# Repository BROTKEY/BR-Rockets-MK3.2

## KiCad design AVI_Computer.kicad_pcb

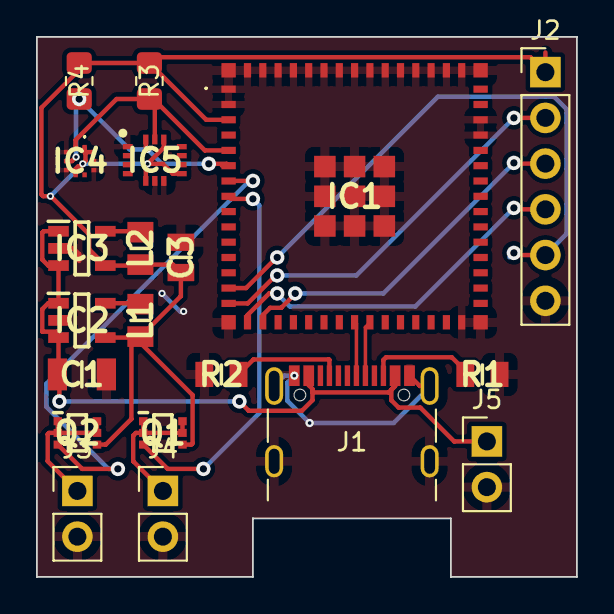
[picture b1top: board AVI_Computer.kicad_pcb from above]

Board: 2 copper layers, 30.0 x 30.0 mm, 20 parts (0 on the bottom side), 19 nets.

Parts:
C1: EMK316B7475KL-T; CAPC3216X180N
C3: TMK212BBJ106KG-T; CAPC2114X145N
IC1: ESP32-S2-MINI-2U-N4; ESP32S2MINI2UN4
IC2, IC3: LM3671MF-3.3_NOPB; SOT95P284X119-5N
IC4: BMP390
IC5: BMI270; QFN50P300X250X87-14N
J1: USB4105-GF-A-060; USB_C_Receptacle_GCT_USB4105-xx-A_16P_TopMnt_Horizontal
J2: Conn_01x06_Pin; PinHeader_1x06_P2.54mm_Vertical
J3, J4, J5: Conn_01x02_Pin; PinHeader_1x02_P2.54mm_Vertical
L1, L2: CBC2012T2R2M; INDC2012X145N
Q1, Q2: SSM6K407TU,LF; SOTFL65P210X75-6N
R1, R2: CR0805-FX-5101ELF; RESC2012X60N
R3, R4: ERJ-P06J472V; R_0805_2012Metric_Pad1.20x1.40mm_HandSolder

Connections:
+3.3V: C3.1, IC1.3 (3V3), IC2.4 (FB), IC3.4 (FB), IC4.1 (VDDIO), IC4.6 (CSB), IC4.10 (VDD), IC5.5 (VDDIO), IC5.8 (VDD), IC5.12 (CSB), J2.1, L1.2, L2.2, Q1.4 (SOURCE), Q2.4 (SOURCE), R3.2, R4.2
+5V: C1.1, IC2.1 (VIN), IC2.3 (EN), IC3.1 (VIN), IC3.3 (EN), J1.A4 (VBUS), J1.A9 (VBUS), J1.B4 (VBUS), J1.B9 (VBUS), J5.1
/CLK: IC1.16 (IO12), J2.4
/CS: IC1.14 (IO10), J2.5
/D+: IC1.24 (IO20), J1.A6 (D+), J1.B6 (D+)
/D-: IC1.23 (IO19), J1.A7 (D-), J1.B7 (D-)
/MISO: IC1.17 (IO13), J2.3
/MOSI: IC1.15 (IO11), J2.2
/Motor1+: J3.1, Q2.1 (DRAIN_1), Q2.2 (DRAIN_2), Q2.5 (DRAIN_3), Q2.6 (DRAIN_4)
/Motor2+: J4.1, Q1.1 (DRAIN_1), Q1.2 (DRAIN_2), Q1.5 (DRAIN_3), Q1.6 (DRAIN_4)
/scl: IC1.5 (IO1), IC4.2 (SCK), IC5.13 (SCX), R3.1
/sda: IC1.6 (IO2), IC4.4 (SDI), IC5.14 (SDX), R4.1
GND: C1.2, C3.2, IC1.1 (GND_1), IC1.2 (GND_2), IC1.30 (GND_3), IC1.42 (GND_4), IC1.43 (GND_5), IC1.46 (GND_6), IC1.47 (GND_7), IC1.48 (GND_8), IC1.49 (GND_9), IC1.50 (GND_10), IC1.51 (GND_11), IC1.52 (GND_12), IC1.53 (GND_13), IC1.54 (GND_14), IC1.55 (GND_15), IC1.56 (GND_16), IC1.57 (GND_17), IC1.58 (GND_18), IC1.59 (GND_19), IC1.60 (GND_20), IC1.61 (GND_21), IC1.62 (GND_22), IC1.63 (GND_23), IC1.64 (GND_24), IC1.65 (GND_25), IC1.66 (GND_26), IC1.67 (GND_27), IC1.68 (GND_28), IC1.69 (GND_29), IC1.70 (GND_30), IC1.71 (GND_31), IC1.72 (GND_32), IC1.73 (GND_33), IC2.2 (GND), IC3.2 (GND), IC4.3 (VSS_1), IC4.5 (SDO), IC4.8 (VSS_2), IC4.9 (VSS_3), IC5.1 (SDO), IC5.6 (GNDIO), IC5.7 (GND), J1.A1 (GND), J1.A12 (GND), J1.B1 (GND), J1.B12 (GND), J1.S1 (SHIELD), J2.6, J3.2, J4.2, J5.2, R1.1, R2.1
unnamed: IC1.7 (IO3), Q2.3 (GATE)
unnamed: IC1.8 (IO4), Q1.3 (GATE)
unnamed: IC2.5 (SW), L1.1
unnamed: IC3.5 (SW), L2.1
unnamed: J1.A5 (CC1), R2.2
unnamed: J1.B5 (CC2), R1.2

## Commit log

2023-03-05 init
2023-03-05 i2c connection
2023-03-05 done some stuff
2023-03-05 cghanges
2023-03-11 do this and that
2023-03-13 sort
2023-03-13 add ORK
2023-03-16 add bodytube draft
2023-03-21 fix bodytupe
